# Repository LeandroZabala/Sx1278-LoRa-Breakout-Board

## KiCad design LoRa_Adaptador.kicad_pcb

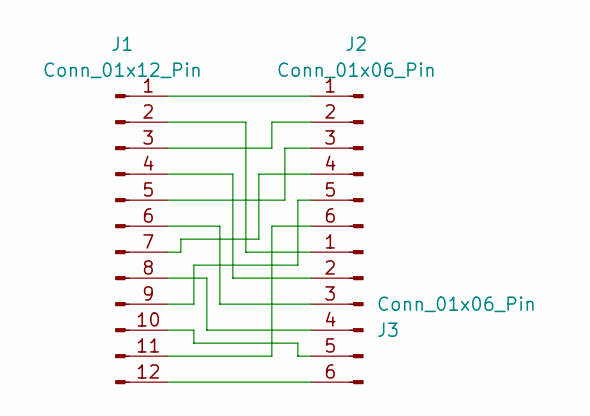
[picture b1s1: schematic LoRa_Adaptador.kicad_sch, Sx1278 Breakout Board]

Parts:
J1: Conn_01x12_Pin; Connector_Edgex12x1.27mm
J2, J3: Conn_01x06_Pin; PinSocket_1x06_P2.54mm_Vertical

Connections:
unnamed: J1.1, J2.1
unnamed: J1.2, J3.1
unnamed: J1.3, J2.2
unnamed: J1.4, J3.2
unnamed: J1.5, J2.3
unnamed: J1.6, J3.3
unnamed: J1.7, J2.4
unnamed: J1.8, J3.4
unnamed: J1.9, J2.5
unnamed: J1.10, J3.5
unnamed: J1.11, J2.6
unnamed: J1.12, J3.6

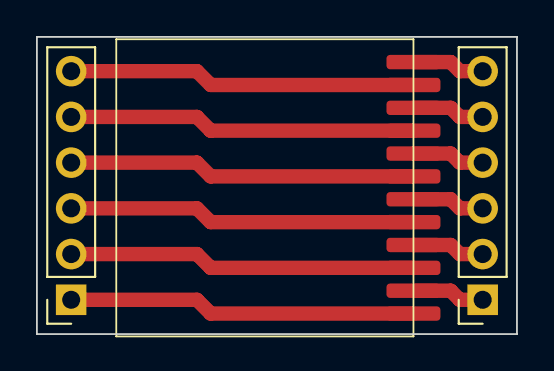
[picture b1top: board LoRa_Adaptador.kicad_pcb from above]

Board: 2 copper layers, 26.7 x 16.5 mm, 3 parts (0 on the bottom side), 12 nets.
